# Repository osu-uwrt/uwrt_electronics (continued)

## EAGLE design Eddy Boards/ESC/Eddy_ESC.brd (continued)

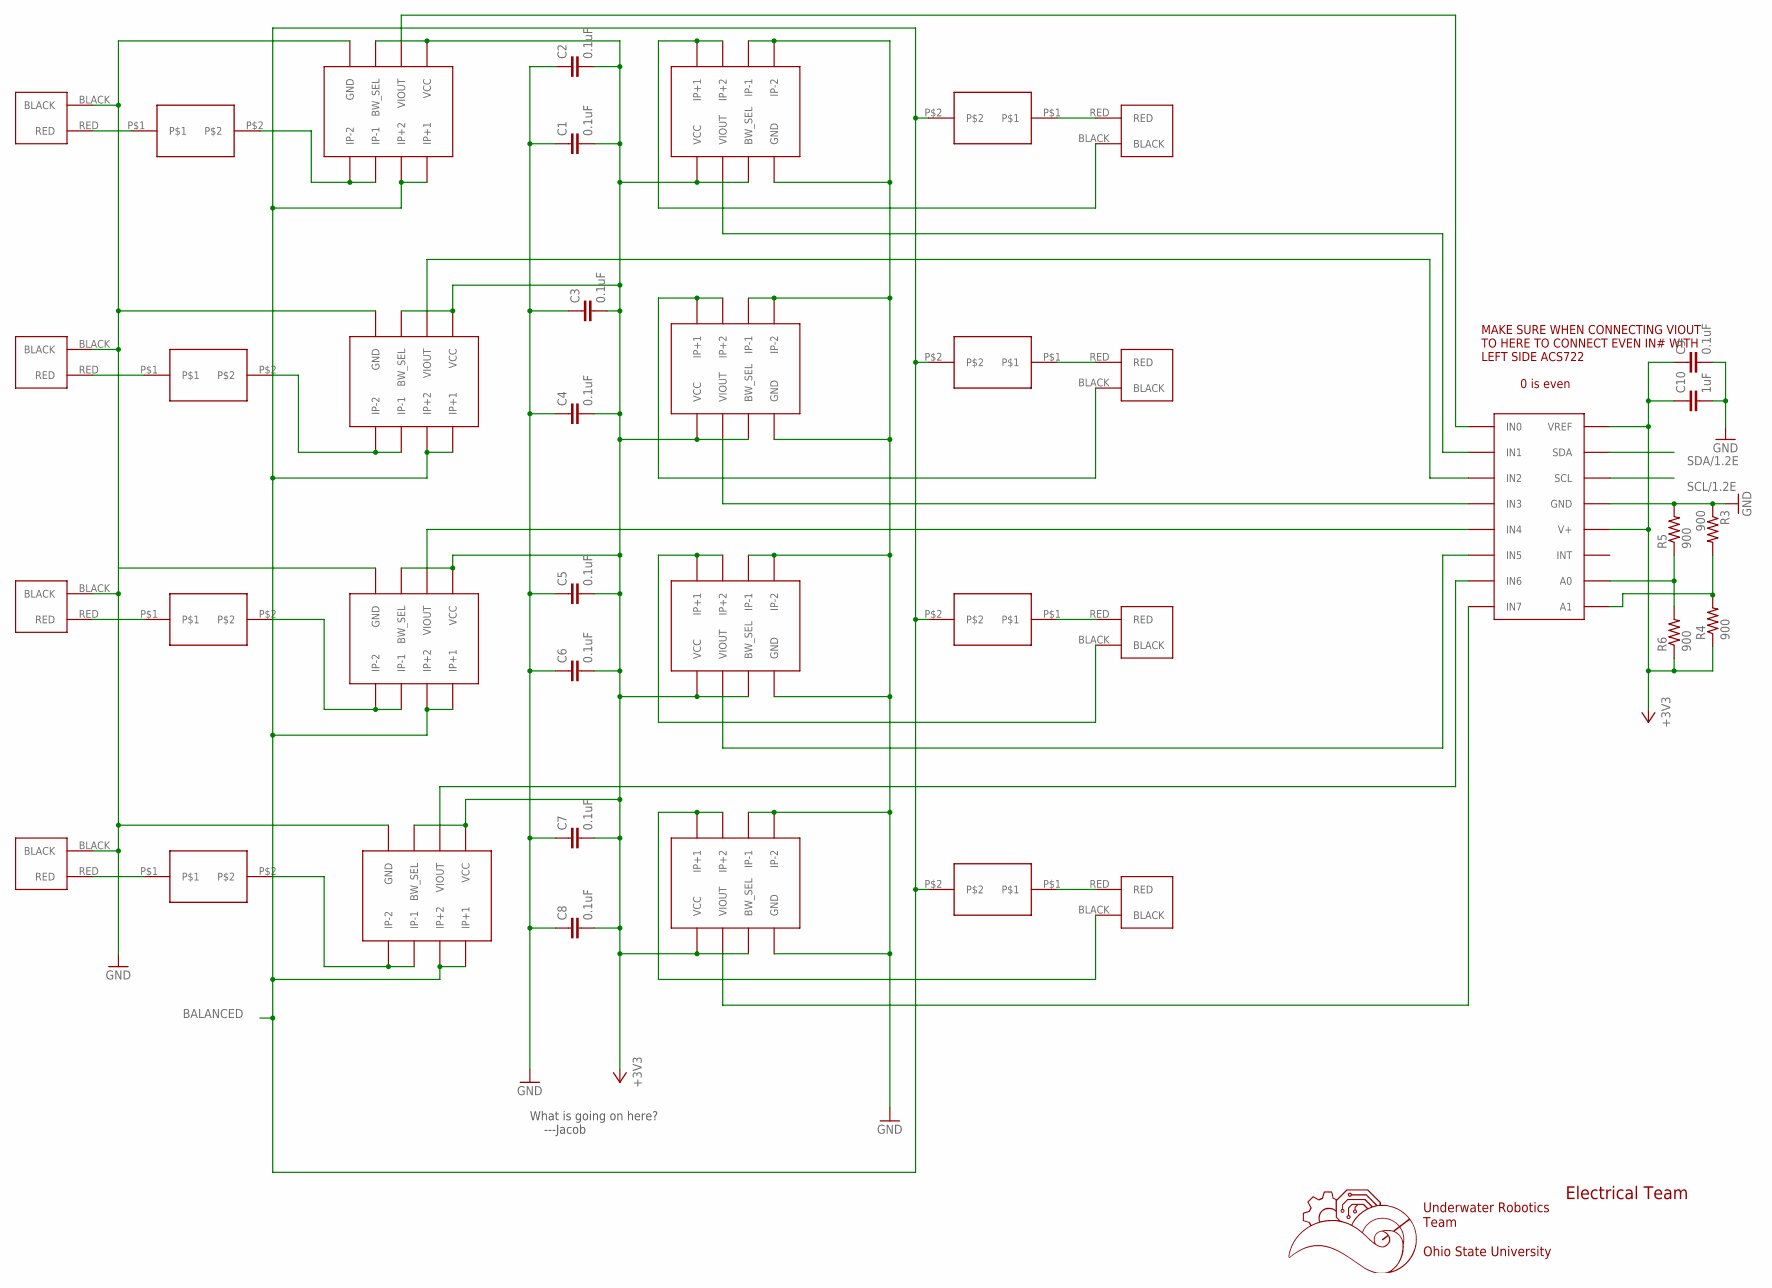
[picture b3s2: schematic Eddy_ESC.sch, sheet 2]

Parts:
C1, C2, C3, C4, C5, C6, C7, C8, C9: 0.1uF; C0603
C10: 1uF; C0603
R3, R4, R5, R6: 900; R0603
U$20, U$21, U$22, U$23, U$24, U$25, U$26, U$27: 1711725
U$28, U$29, U$30, U$31, U$32, U$33, U$34, U$35: ACS722; SOIC-8
U$36: ADC128D818; TSSOP-16
U$37, U$38, U$39, U$40, U$41, U$42, U$43, U$44: 1206SFH

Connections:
+3V3: C1.2, C2.2, C3.2, C4.2, C5.2, C6.2, C7.2, C8.2, C9.1, C10.1, R4.1, R6.1, U$28.BW_SEL, U$28.VCC, U$29.BW_SEL, U$29.VCC, U$30.BW_SEL, U$30.VCC, U$31.BW_SEL, U$31.VCC, U$32.BW_SEL, U$32.VCC, U$33.BW_SEL, U$33.VCC, U$34.BW_SEL, U$34.VCC, U$35.BW_SEL, U$35.VCC, U$36.V+, U$36.VREF; also elsewhere on the board
BALANCED: U$32.IP+1, U$32.IP+2, U$33.IP+1, U$33.IP+2, U$34.IP+1, U$34.IP+2, U$35.IP+1, U$35.IP+2, U$41.P$2, U$42.P$2, U$43.P$2, U$44.P$2
unnamed: U$20.BLACK, U$28.IP+1, U$28.IP+2
unnamed: U$21.BLACK, U$29.IP+1, U$29.IP+2
unnamed: U$34.VIOUT, U$36.IN4
unnamed: U$29.VIOUT, U$36.IN3
unnamed: U$22.BLACK, U$30.IP+1, U$30.IP+2
unnamed: U$33.IP-1, U$33.IP-2, U$38.P$2
unnamed: U$34.IP-1, U$34.IP-2, U$39.P$2
unnamed: U$31.VIOUT, U$36.IN7
unnamed: U$35.VIOUT, U$36.IN6
unnamed: U$30.VIOUT, U$36.IN5
unnamed: U$32.IP-1, U$32.IP-2, U$37.P$2
unnamed: U$35.IP-1, U$35.IP-2, U$40.P$2
unnamed: U$33.VIOUT, U$36.IN2
unnamed: U$28.VIOUT, U$36.IN1
unnamed: U$32.VIOUT, U$36.IN0
unnamed: U$24.RED, U$37.P$1
unnamed: U$25.RED, U$38.P$1
unnamed: U$26.RED, U$39.P$1
unnamed: U$27.RED, U$40.P$1
unnamed: U$20.RED, U$41.P$1
unnamed: U$21.RED, U$42.P$1
unnamed: U$22.RED, U$43.P$1
unnamed: U$23.RED, U$44.P$1
unnamed: R5.1, R6.2, U$36.A0
unnamed: R3.2, R4.2, U$36.A1
SCL/1.2E: U$36.SCL
SDA/1.2E: U$36.SDA

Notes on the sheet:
Underwater Robotics Team Ohio State University
Electrical Team
MAKE SURE WHEN CONNECTING VIOUT TO HERE TO CONNECT EVEN IN# WITH LEFT SIDE ACS722 0 is even
What is going on here? ---Jacob

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
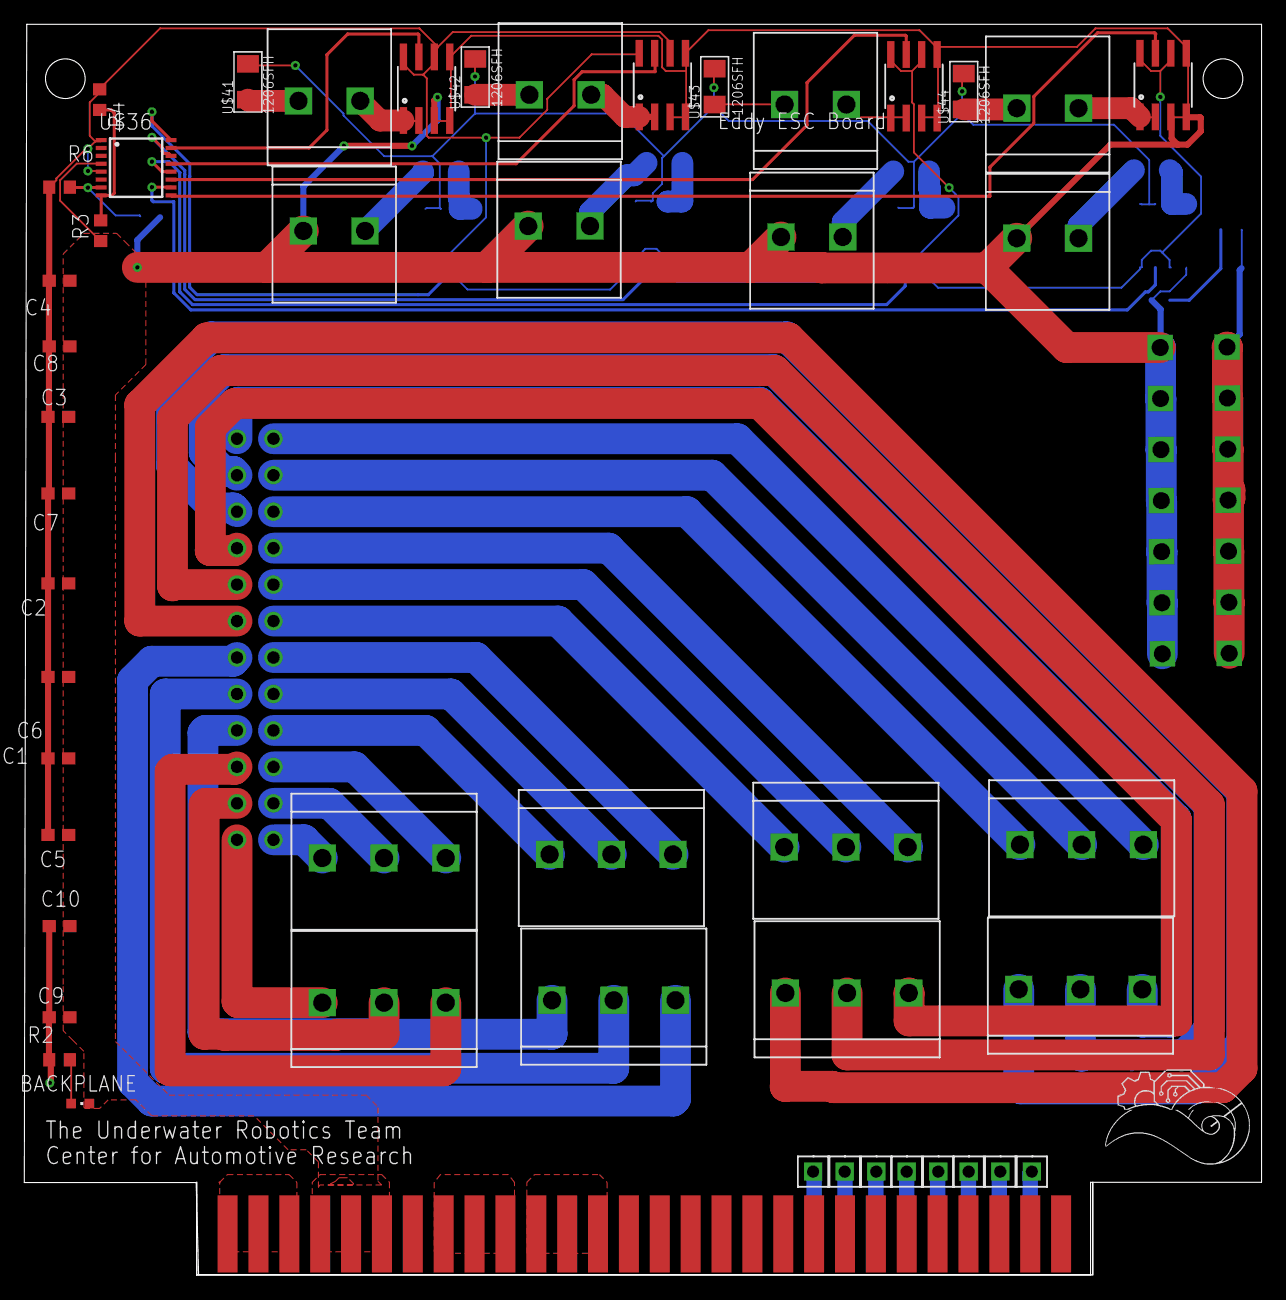
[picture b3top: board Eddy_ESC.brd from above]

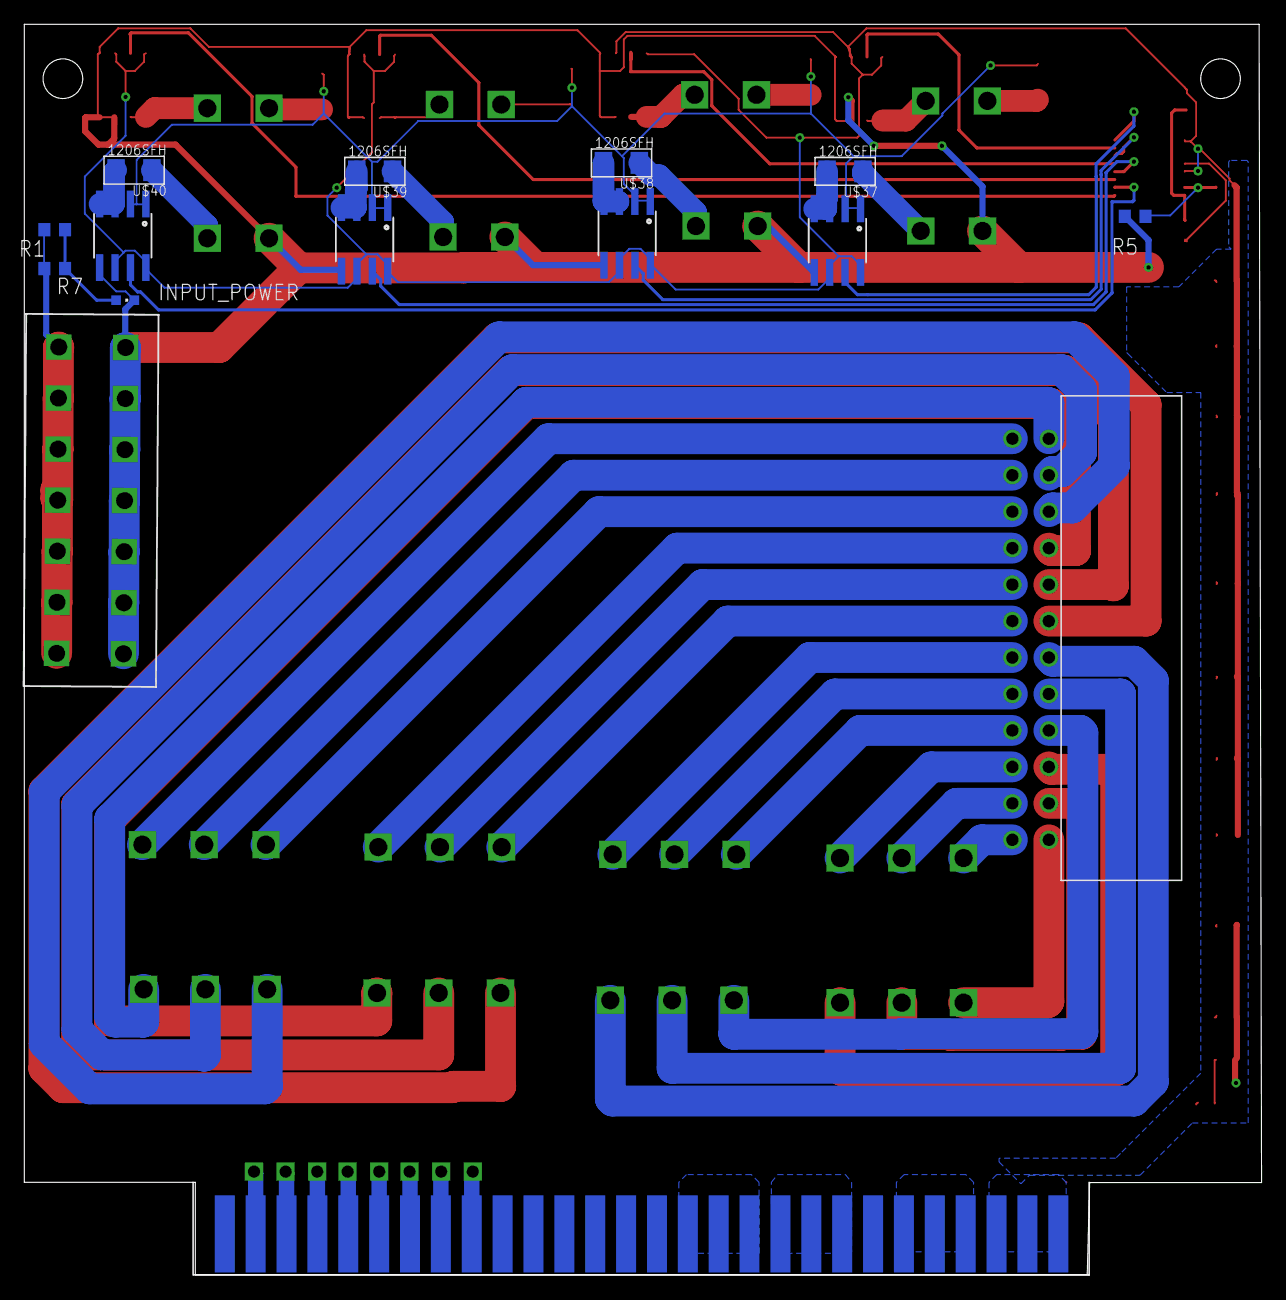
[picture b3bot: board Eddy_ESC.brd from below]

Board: 2 copper layers, 101.8 x 102.9 mm, 63 parts (14 on the bottom side), 64 nets.

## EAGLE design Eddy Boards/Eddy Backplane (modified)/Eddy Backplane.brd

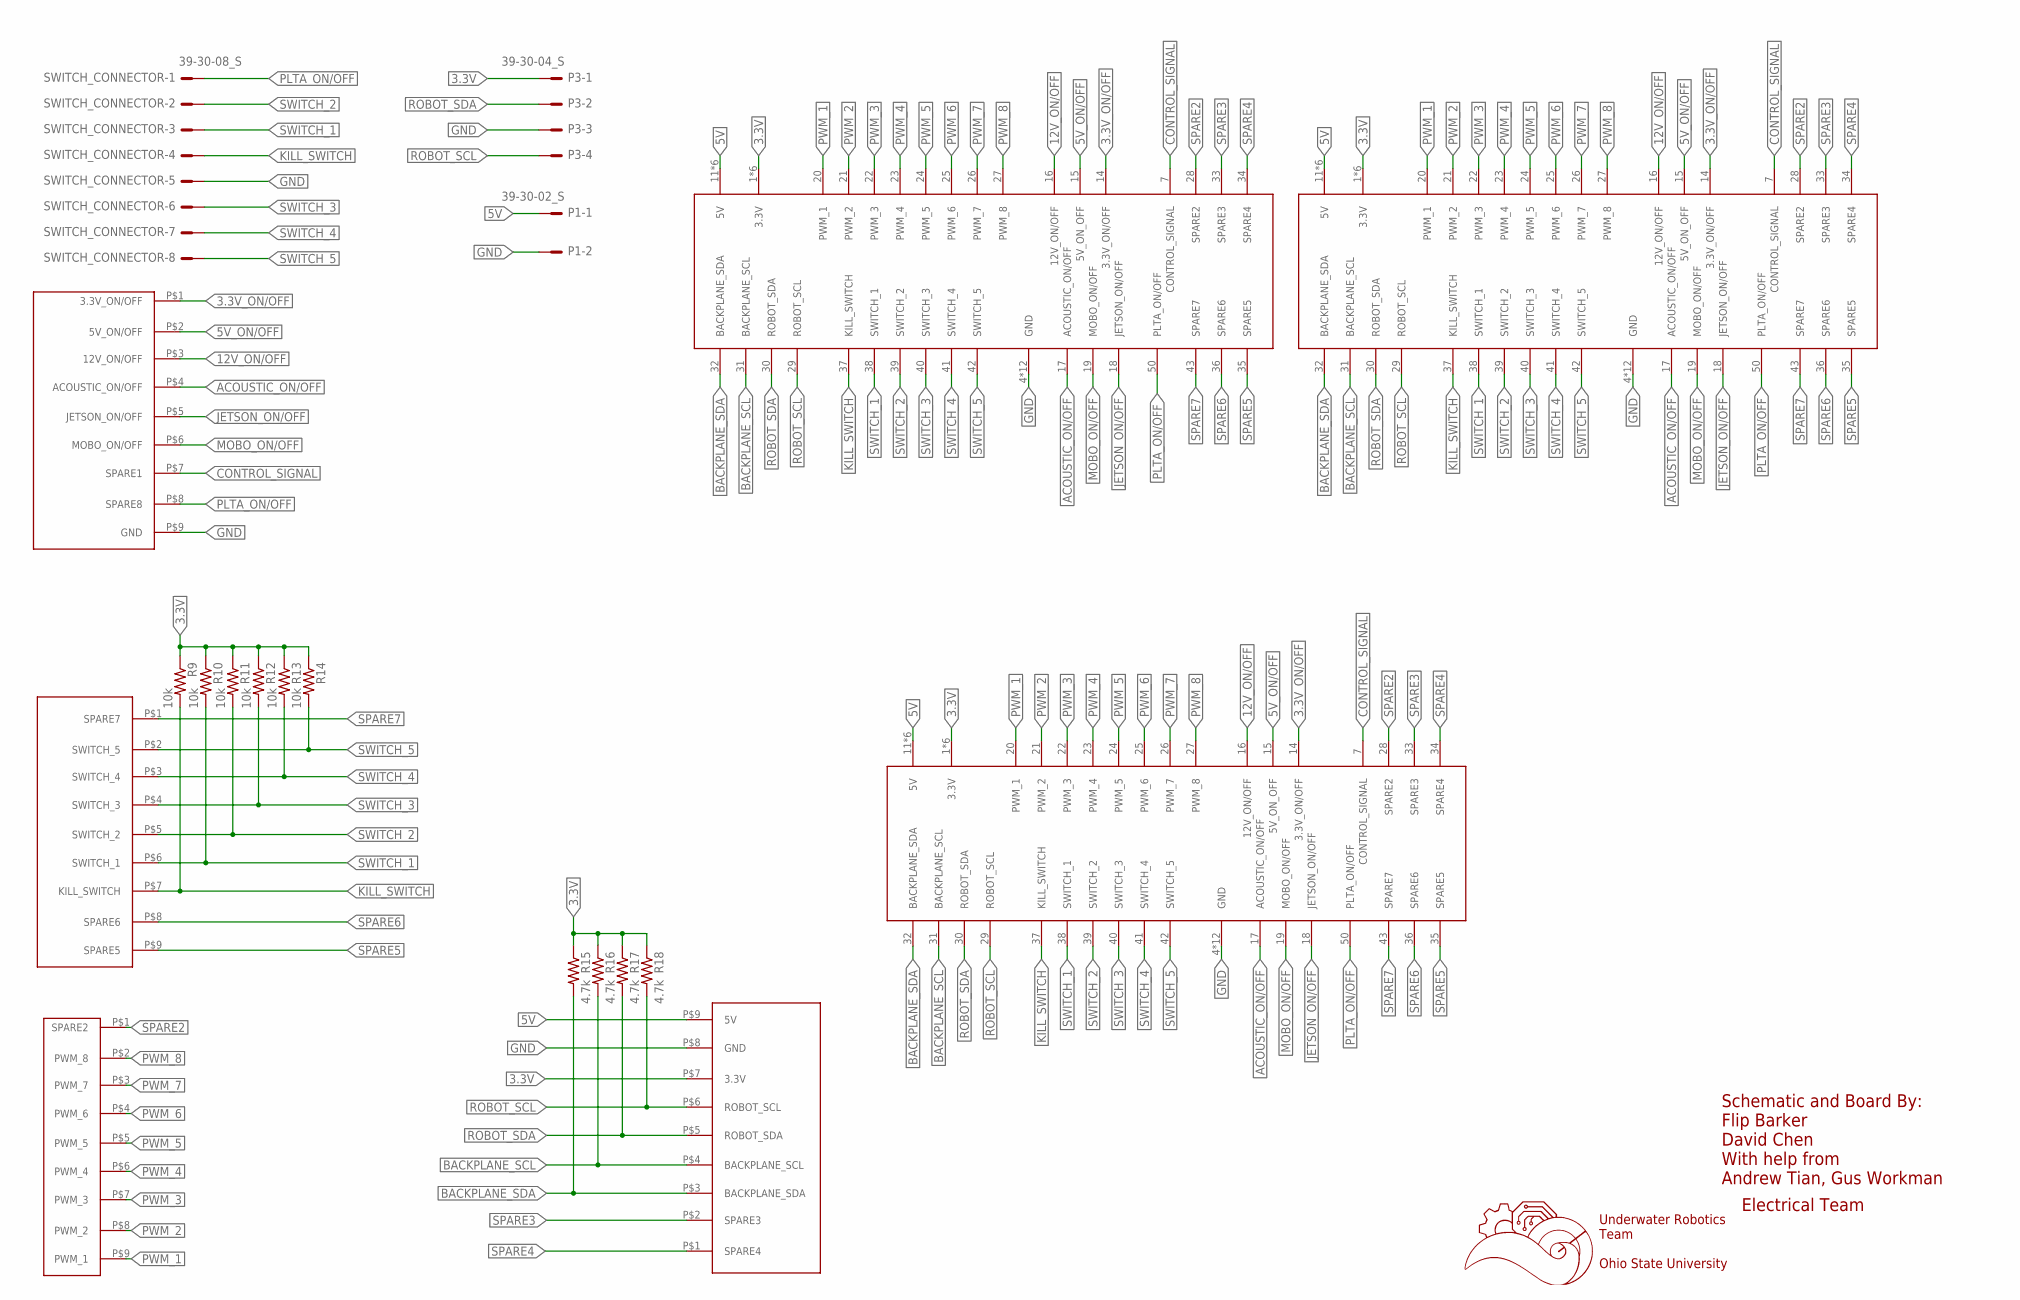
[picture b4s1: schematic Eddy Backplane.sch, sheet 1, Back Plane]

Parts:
P1: 39-30-02_S; 39-30-?02?
P3: 39-30-04_S; 39-30-?04?
PWR_ON: 929870-01-09_3; 929852-01-09_1ROW
R9, R10, R11, R12, R13, R14: 10k; R0603
R15, R16, R17, R18: 4.7k; R0603
SWITCH_CONN: 929870-01-09_1; 929852-01-09_1ROW
SWITCH_CONNECTOR: 39-30-08_S; 39-30-?08?
U$1, U$2, U$3: 5530843-FEMALE; 5530843-6-BACKPLANEMATE
U$6: 929870-01-09_2; 929852-01-09_1ROW
U$8: 929870-01-09_4; 929852-01-09_1ROW

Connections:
3.3V: P3.1, R9.1, R10.1, R11.1, R12.1, R13.1, R14.1, R15.1, R16.1, R17.1, R18.1, U$1.1 (3.3V), U$1.2 (3.3V), U$1.3 (3.3V), U$1.54 (3.3V), U$1.55 (3.3V), U$1.56 (3.3V), U$2.1 (3.3V), U$2.2 (3.3V), U$2.3 (3.3V), U$2.54 (3.3V), U$2.55 (3.3V), U$2.56 (3.3V), U$3.1 (3.3V), U$3.2 (3.3V), U$3.3 (3.3V), U$3.54 (3.3V), U$3.55 (3.3V), U$3.56 (3.3V), U$8.P$7 (3.3V); also elsewhere on the board
3.3V_ON/OFF: PWR_ON.P$1 (3.3V_ON/OFF), U$1.14 (3.3V_ON/OFF), U$2.14 (3.3V_ON/OFF), U$3.14 (3.3V_ON/OFF); also elsewhere on the board
5V: P1.1, U$1.11 (5V), U$1.12 (5V), U$1.13 (5V), U$1.44 (5V), U$1.45 (5V), U$1.46 (5V), U$2.11 (5V), U$2.12 (5V), U$2.13 (5V), U$2.44 (5V), U$2.45 (5V), U$2.46 (5V), U$3.11 (5V), U$3.12 (5V), U$3.13 (5V), U$3.44 (5V), U$3.45 (5V), U$3.46 (5V), U$8.P$9 (5V); also elsewhere on the board
5V_ON/OFF: PWR_ON.P$2 (5V_ON/OFF), U$1.15 (5V_ON_OFF), U$2.15 (5V_ON_OFF), U$3.15 (5V_ON_OFF); also elsewhere on the board
12V_ON/OFF: PWR_ON.P$3 (12V_ON/OFF), U$1.16 (12V_ON/OFF), U$2.16 (12V_ON/OFF), U$3.16 (12V_ON/OFF); also elsewhere on the board
ACOUSTIC_ON/OFF: PWR_ON.P$4 (ACOUSTIC_ON/OFF), U$1.17 (ACOUSTIC_ON/OFF), U$2.17 (ACOUSTIC_ON/OFF), U$3.17 (ACOUSTIC_ON/OFF)
BACKPLANE_SCL: R16.2, U$1.31 (BACKPLANE_SCL), U$2.31 (BACKPLANE_SCL), U$3.31 (BACKPLANE_SCL), U$8.P$4 (BACKPLANE_SCL); also elsewhere on the board
BACKPLANE_SDA: R15.2, U$1.32 (BACKPLANE_SDA), U$2.32 (BACKPLANE_SDA), U$3.32 (BACKPLANE_SDA), U$8.P$3 (BACKPLANE_SDA); also elsewhere on the board
CONTROL_SIGNAL: PWR_ON.P$7 (SPARE1), U$1.7 (CONTROL_SIGNAL), U$2.7 (CONTROL_SIGNAL), U$3.7 (CONTROL_SIGNAL); also elsewhere on the board
GND: P1.2, P3.3, PWR_ON.P$9 (GND), SWITCH_CONNECTOR.5, U$1.4 (GND), U$1.5 (GND), U$1.6 (GND), U$1.8 (GND), U$1.9 (GND), U$1.10 (GND), U$1.47 (GND), U$1.48 (GND), U$1.49 (GND), U$1.51 (GND), U$1.52 (GND), U$1.53 (GND), U$2.4 (GND), U$2.5 (GND), U$2.6 (GND), U$2.8 (GND), U$2.9 (GND), U$2.10 (GND), U$2.47 (GND), U$2.48 (GND), U$2.49 (GND), U$2.51 (GND), U$2.52 (GND), U$2.53 (GND), U$3.4 (GND), U$3.5 (GND), U$3.6 (GND), U$3.8 (GND), U$3.9 (GND), U$3.10 (GND), U$3.47 (GND), U$3.48 (GND), U$3.49 (GND), U$3.51 (GND), U$3.52 (GND), U$3.53 (GND), U$8.P$8 (GND); also elsewhere on the board
JETSON_ON/OFF: PWR_ON.P$5 (JETSON_ON/OFF), U$1.18 (JETSON_ON/OFF), U$2.18 (JETSON_ON/OFF), U$3.18 (JETSON_ON/OFF); also elsewhere on the board
KILL_SWITCH: R9.2, SWITCH_CONN.P$7 (KILL_SWITCH), SWITCH_CONNECTOR.4, U$1.37 (KILL_SWITCH), U$2.37 (KILL_SWITCH), U$3.37 (KILL_SWITCH); also elsewhere on the board
MOBO_ON/OFF: PWR_ON.P$6 (MOBO_ON/OFF), U$1.19 (MOBO_ON/OFF), U$2.19 (MOBO_ON/OFF), U$3.19 (MOBO_ON/OFF); also elsewhere on the board
PLTA_ON/OFF: PWR_ON.P$8 (SPARE8), SWITCH_CONNECTOR.1, U$1.50 (PLTA_ON/OFF), U$2.50 (PLTA_ON/OFF), U$3.50 (PLTA_ON/OFF)
PWM_1: U$1.20 (PWM_1), U$2.20 (PWM_1), U$3.20 (PWM_1), U$6.P$9 (PWM_1); also elsewhere on the board
PWM_2: U$1.21 (PWM_2), U$2.21 (PWM_2), U$3.21 (PWM_2), U$6.P$8 (PWM_2); also elsewhere on the board
PWM_3: U$1.22 (PWM_3), U$2.22 (PWM_3), U$3.22 (PWM_3), U$6.P$7 (PWM_3); also elsewhere on the board
PWM_4: U$1.23 (PWM_4), U$2.23 (PWM_4), U$3.23 (PWM_4), U$6.P$6 (PWM_4); also elsewhere on the board
PWM_5: U$1.24 (PWM_5), U$2.24 (PWM_5), U$3.24 (PWM_5), U$6.P$5 (PWM_5); also elsewhere on the board
PWM_6: U$1.25 (PWM_6), U$2.25 (PWM_6), U$3.25 (PWM_6), U$6.P$4 (PWM_6); also elsewhere on the board
PWM_7: U$1.26 (PWM_7), U$2.26 (PWM_7), U$3.26 (PWM_7), U$6.P$3 (PWM_7); also elsewhere on the board
PWM_8: U$1.27 (PWM_8), U$2.27 (PWM_8), U$3.27 (PWM_8), U$6.P$2 (PWM_8); also elsewhere on the board
ROBOT_SCL: P3.4, R18.2, U$1.29 (ROBOT_SCL), U$2.29 (ROBOT_SCL), U$3.29 (ROBOT_SCL), U$8.P$6 (ROBOT_SCL); also elsewhere on the board
ROBOT_SDA: P3.2, R17.2, U$1.30 (ROBOT_SDA), U$2.30 (ROBOT_SDA), U$3.30 (ROBOT_SDA), U$8.P$5 (ROBOT_SDA); also elsewhere on the board
SPARE2: U$1.28 (SPARE2), U$2.28 (SPARE2), U$3.28 (SPARE2), U$6.P$1 (SPARE2)
SPARE3: U$1.33 (SPARE3), U$2.33 (SPARE3), U$3.33 (SPARE3), U$8.P$2 (SPARE3)
SPARE4: U$1.34 (SPARE4), U$2.34 (SPARE4), U$3.34 (SPARE4), U$8.P$1 (SPARE4)
SPARE5: SWITCH_CONN.P$9 (SPARE5), U$1.35 (SPARE5), U$2.35 (SPARE5), U$3.35 (SPARE5)
SPARE6: SWITCH_CONN.P$8 (SPARE6), U$1.36 (SPARE6), U$2.36 (SPARE6), U$3.36 (SPARE6)
SPARE7: SWITCH_CONN.P$1 (SPARE7), U$1.43 (SPARE7), U$2.43 (SPARE7), U$3.43 (SPARE7)
SWITCH_1: R10.2, SWITCH_CONN.P$6 (SWITCH_1), SWITCH_CONNECTOR.3, U$1.38 (SWITCH_1), U$2.38 (SWITCH_1), U$3.38 (SWITCH_1); also elsewhere on the board
SWITCH_2: R11.2, SWITCH_CONN.P$5 (SWITCH_2), SWITCH_CONNECTOR.2, U$1.39 (SWITCH_2), U$2.39 (SWITCH_2), U$3.39 (SWITCH_2); also elsewhere on the board
SWITCH_3: R12.2, SWITCH_CONN.P$4 (SWITCH_3), SWITCH_CONNECTOR.6, U$1.40 (SWITCH_3), U$2.40 (SWITCH_3), U$3.40 (SWITCH_3); also elsewhere on the board
SWITCH_4: R13.2, SWITCH_CONN.P$3 (SWITCH_4), SWITCH_CONNECTOR.7, U$1.41 (SWITCH_4), U$2.41 (SWITCH_4), U$3.41 (SWITCH_4); also elsewhere on the board
SWITCH_5: R14.2, SWITCH_CONN.P$2 (SWITCH_5), SWITCH_CONNECTOR.8, U$1.42 (SWITCH_5), U$2.42 (SWITCH_5), U$3.42 (SWITCH_5); also elsewhere on the board

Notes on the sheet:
Underwater Robotics Team Ohio State University
Electrical Team
Schematic and Board By: Flip Barker David Chen With help from Andrew Tian, Gus Workman

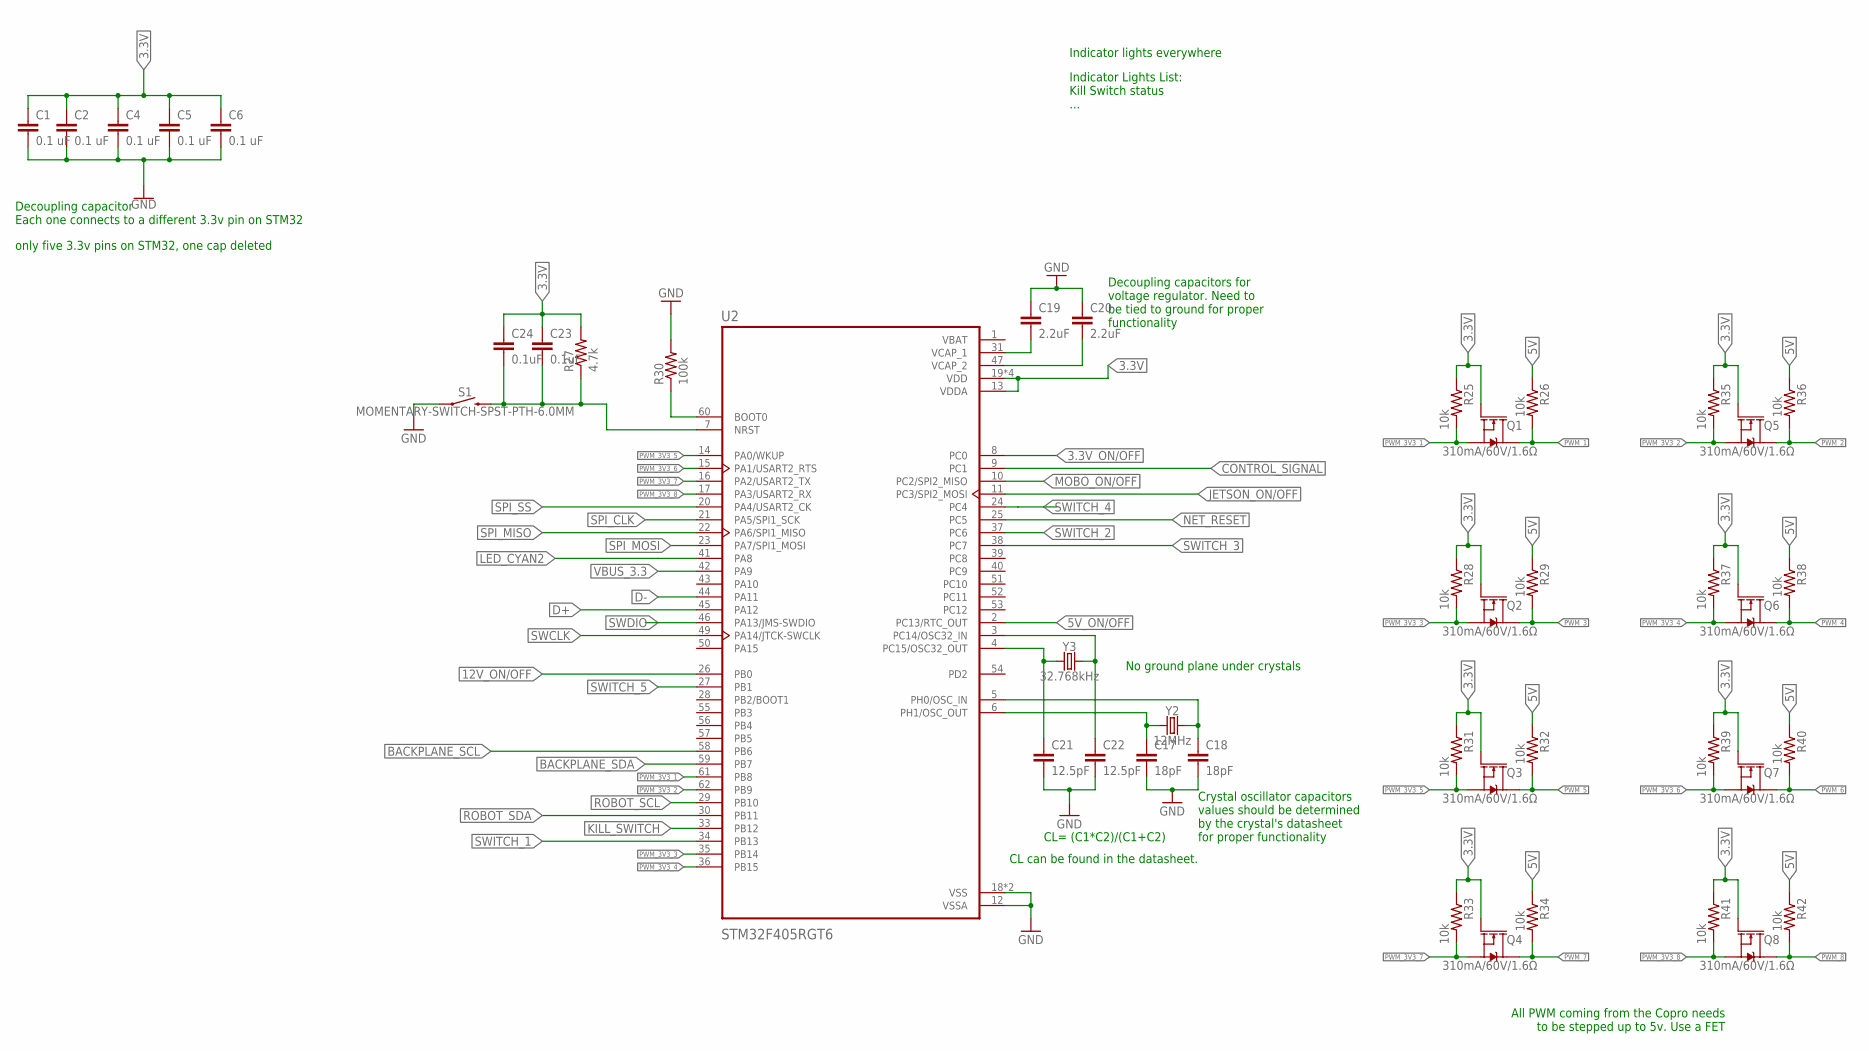
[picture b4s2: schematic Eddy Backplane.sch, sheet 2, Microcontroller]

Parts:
C1, C2, C4, C5, C6: 0.1 uF; C0603
C17, C18: 18pF; C0603
C19, C20: 2.2uF; C0603
C21, C22: 12.5pF; C0603
C23, C24: 0.1uF; C0603
Q1, Q2, Q3, Q4, Q5, Q6, Q7, Q8: 310mA/60V/1.6Ω; SOT323
R25, R26, R28, R29, R31, R32, R33, R34, R35, R36, R37, R38, R39, R40, R41, R42: 10k; R0603
R27: 4.7k; R0603
R30: 100k; R0603
S1: MOMENTARY-SWITCH-SPST-PTH-6.0MM; TACTILE_SWITCH_PTH_6.0MM
U2: STM32F405RGT6; QFP50P1200X1200X160-64N
Y2: 12MHz; HC49US
Y3: 32.768kHz; CRYSTAL-SMD-3.2X1.5MM

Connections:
3.3V: C1.1, C2.1, C4.1, C5.1, C6.1, C23.1, C24.1, Q1.1 (G), Q2.1 (G), Q3.1 (G), Q4.1 (G), Q5.1 (G), Q6.1 (G), Q7.1 (G), Q8.1 (G), R25.1, R27.2, R28.1, R31.1, R33.1, R35.1, R37.1, R39.1, R41.1, U2.13 (VDDA), U2.19 (VDD), U2.32 (VDD), U2.48 (VDD), U2.64 (VDD); also elsewhere on the board
3.3V_ON/OFF: U2.8 (PC0); also elsewhere on the board
5V: R26.1, R29.1, R32.1, R34.1, R36.1, R38.1, R40.1, R42.1; also elsewhere on the board
5V_ON/OFF: U2.2 (PC13/RTC_OUT); also elsewhere on the board
12V_ON/OFF: U2.26 (PB0); also elsewhere on the board
BACKPLANE_SCL: U2.58 (PB6); also elsewhere on the board
BACKPLANE_SDA: U2.59 (PB7); also elsewhere on the board
CONTROL_SIGNAL: U2.9 (PC1); also elsewhere on the board
D+: U2.45 (PA12); also elsewhere on the board
D-: U2.44 (PA11); also elsewhere on the board
GND: C1.2, C2.2, C4.2, C5.2, C6.2, C17.2, C18.2, C19.1, C20.1, C21.2, C22.2, R30.2, S1.1, U2.12 (VSSA), U2.18 (VSS), U2.63 (VSS); also elsewhere on the board
JETSON_ON/OFF: U2.11 (PC3/SPI2_MOSI); also elsewhere on the board
KILL_SWITCH: U2.33 (PB12); also elsewhere on the board
LED_CYAN2: U2.41 (PA8)
MOBO_ON/OFF: U2.10 (PC2/SPI2_MISO); also elsewhere on the board
unnamed: C17.1, U2.6 (PH1/OSC_OUT), Y2.1
unnamed: C18.1, U2.5 (PH0/OSC_IN), Y2.2
unnamed: C20.2, U2.47 (VCAP_2)
unnamed: C19.2, U2.31 (VCAP_1)
unnamed: C21.1, U2.4 (PC15/OSC32_OUT), Y3.P$1 (1)
unnamed: C22.1, U2.3 (PC14/OSC32_IN), Y3.P$2 (2)
unnamed: R30.1, U2.60 (BOOT0)
unnamed: C23.2, C24.2, R27.1, S1.3 (2), U2.7 (NRST)
NET_RESET: U2.25 (PC5); also elsewhere on the board
PWM_1: Q1.3 (D), R26.2; also elsewhere on the board
PWM_2: Q5.3 (D), R36.2; also elsewhere on the board
PWM_3: Q2.3 (D), R29.2; also elsewhere on the board
PWM_3V3_1: Q1.2 (S), R25.2, U2.61 (PB8)
PWM_3V3_2: Q5.2 (S), R35.2, U2.62 (PB9)
PWM_3V3_3: Q2.2 (S), R28.2, U2.35 (PB14)
PWM_3V3_4: Q6.2 (S), R37.2, U2.36 (PB15)
PWM_3V3_5: Q3.2 (S), R31.2, U2.14 (PA0/WKUP)
PWM_3V3_6: Q7.2 (S), R39.2, U2.15 (PA1/USART2_RTS)
PWM_3V3_7: Q4.2 (S), R33.2, U2.16 (PA2/USART2_TX)
PWM_3V3_8: Q8.2 (S), R41.2, U2.17 (PA3/USART2_RX)
PWM_4: Q6.3 (D), R38.2; also elsewhere on the board
PWM_5: Q3.3 (D), R32.2; also elsewhere on the board
PWM_6: Q7.3 (D), R40.2; also elsewhere on the board
PWM_7: Q4.3 (D), R34.2; also elsewhere on the board
PWM_8: Q8.3 (D), R42.2; also elsewhere on the board
ROBOT_SCL: U2.29 (PB10); also elsewhere on the board
ROBOT_SDA: U2.30 (PB11); also elsewhere on the board
SPI_CLK: U2.21 (PA5/SPI1_SCK); also elsewhere on the board
SPI_MISO: U2.22 (PA6/SPI1_MISO); also elsewhere on the board
SPI_MOSI: U2.23 (PA7/SPI1_MOSI); also elsewhere on the board
SPI_SS: U2.20 (PA4/USART2_CK); also elsewhere on the board
SWCLK: U2.49 (PA14/JTCK-SWCLK); also elsewhere on the board
SWDIO: U2.46 (PA13/JMS-SWDIO); also elsewhere on the board
SWITCH_1: U2.34 (PB13); also elsewhere on the board
SWITCH_2: U2.37 (PC6); also elsewhere on the board
SWITCH_3: U2.38 (PC7); also elsewhere on the board
SWITCH_4: U2.24 (PC4); also elsewhere on the board
SWITCH_5: U2.27 (PB1); also elsewhere on the board
VBAT: U2.1 (VBAT)
VBUS_3.3: U2.42 (PA9); also elsewhere on the board

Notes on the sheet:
Decoupling capacitor Each one connects to a different 3.3v pin on STM32
Indicator lights everywhere
Decoupling capacitors for voltage regulator. Need to be tied to ground for proper functionality
Crystal oscillator capacitors values should be determined by the crystal's datasheet for proper functionality
All PWM coming from the Copro needs to be stepped up to 5v. Use a FET
CL= (C1*C2)/(C1+C2)
CL can be found in the datasheet.
No ground plane under crystals
Indicator Lights List: Kill Switch status ...
only five 3.3v pins on STM32, one cap deleted

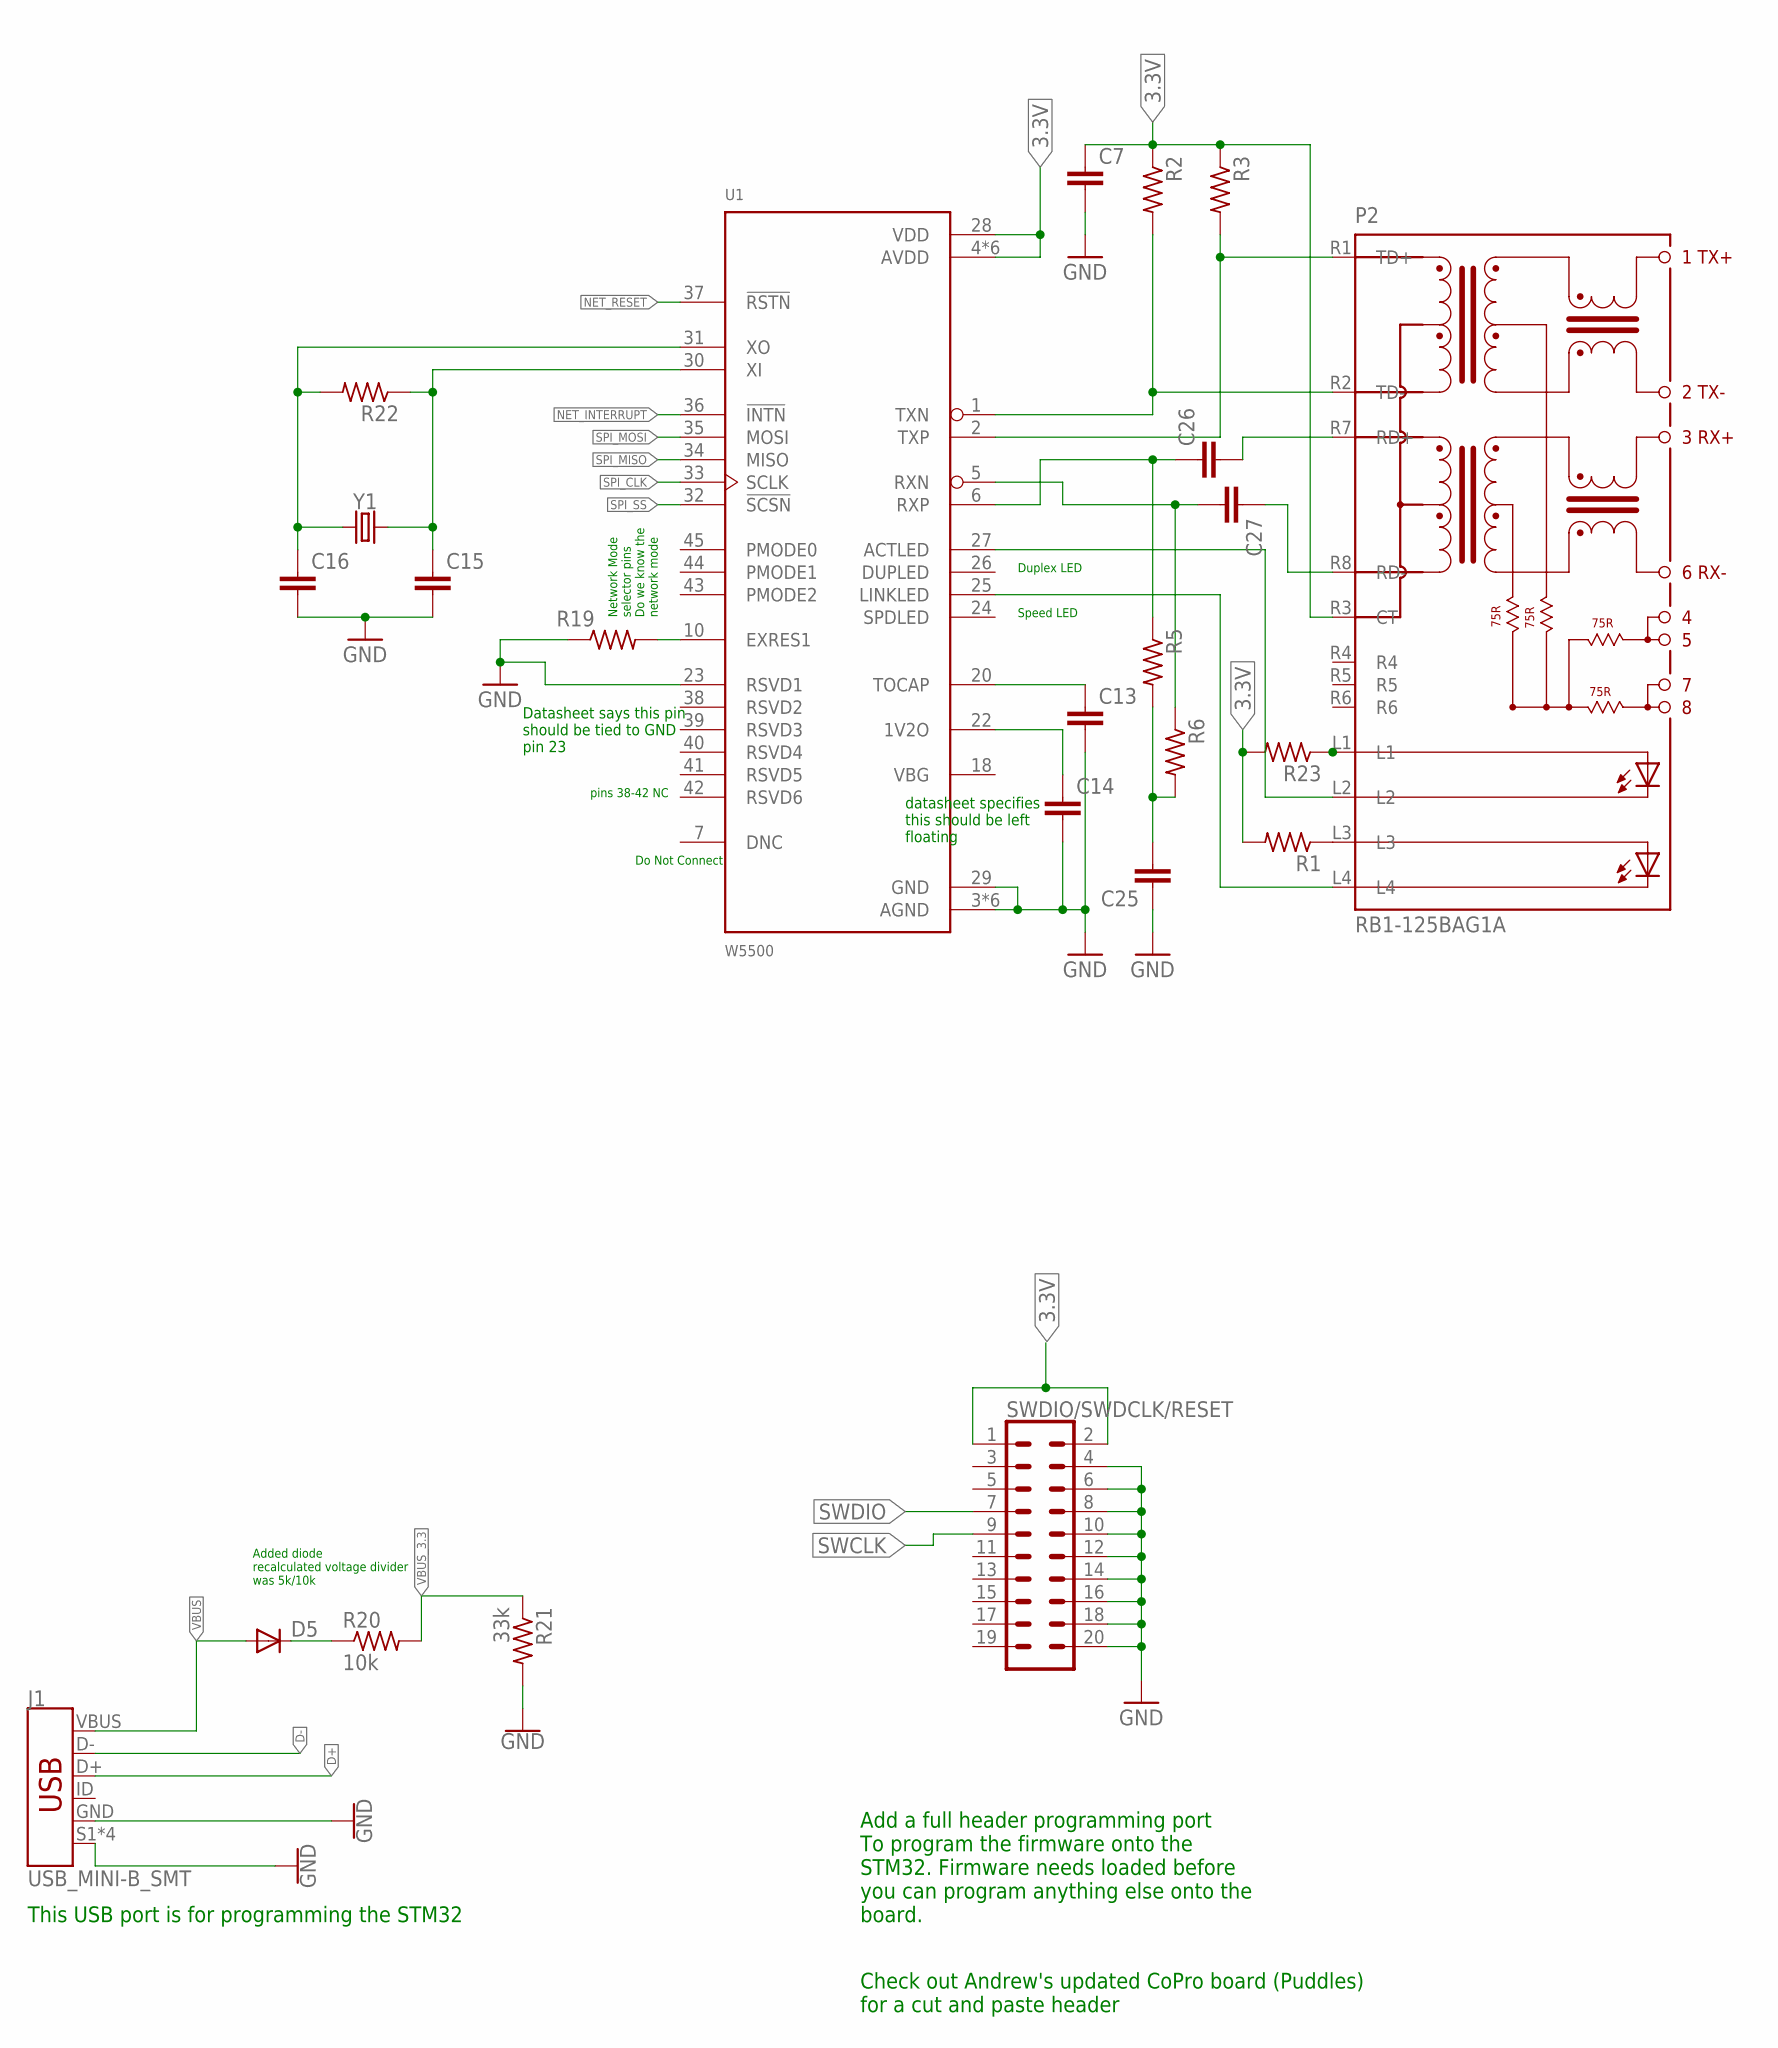
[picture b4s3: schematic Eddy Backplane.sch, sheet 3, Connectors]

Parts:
C7, C13, C14, C15, C16, C25, C26, C27: C-EUC0603; C0603
D5: DIODE-SMB; SMB
J1: USB_MINI-B_SMT; USB-MINIB
P2: RB1-125BAG1A; WIZNET_RB1-125BAG1A
R1, R2, R3, R5, R6, R19, R22, R23: R-US_R0603; R0603
R20: 10k; R0603
R21: 33k; R0603
SWDIO/SWDCLK/RESET: CONN_10X2; 2X10
U1: W5500; QFP50P900X900X160-48N
Y1: CRYSTALPTH-HC49US; HC49US

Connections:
3.3V: C7.1, P2.R3 (CT), R1.2, R2.1, R3.1, R23.2, SWDIO/SWDCLK/RESET.1, SWDIO/SWDCLK/RESET.2, U1.4 (AVDD), U1.8 (AVDD), U1.11 (AVDD), U1.15 (AVDD), U1.17 (AVDD), U1.21 (AVDD), U1.28 (VDD); also elsewhere on the board
D+: J1.D+; also elsewhere on the board
D-: J1.D-; also elsewhere on the board
GND: C7.2, C13.2, C14.2, C15.2, C16.2, C25.1, J1.GND, J1.S1 (SHIELD), J1.S2 (SHIELD), J1.S3 (SHIELD), J1.S4 (SHIELD), R19.1, R21.2, SWDIO/SWDCLK/RESET.4, SWDIO/SWDCLK/RESET.6, SWDIO/SWDCLK/RESET.8, SWDIO/SWDCLK/RESET.10, SWDIO/SWDCLK/RESET.12, SWDIO/SWDCLK/RESET.14, SWDIO/SWDCLK/RESET.16, SWDIO/SWDCLK/RESET.18, SWDIO/SWDCLK/RESET.20, U1.3 (AGND), U1.9 (AGND), U1.14 (AGND), U1.16 (AGND), U1.19 (AGND), U1.23 (RSVD1), U1.29 (GND), U1.48 (AGND); also elsewhere on the board
unnamed: C14.1, U1.22 (1V2O)
unnamed: D5.C, R20.1
unnamed: C15.1, R22.1, U1.30 (XI), Y1.2
unnamed: C16.1, R22.2, U1.31 (XO), Y1.1
unnamed: P2.L4, U1.25 (LINKLED)
unnamed: P2.L2, U1.27 (ACTLED)
unnamed: C13.1, U1.20 (TOCAP)
unnamed: R19.2, U1.10 (EXRES1)
unnamed: P2.L1, R23.1
unnamed: P2.L3, R1.1
unnamed: C25.2, R5.2, R6.2
unnamed: P2.R1 (TD+), R3.2, U1.2 (TXP)
unnamed: P2.R2 (TD-), R2.2, U1.1 (TXN)
unnamed: C26.2, P2.R7 (RD+)
unnamed: C26.1, R5.1, U1.6 (RXP)
unnamed: C27.2, R6.1, U1.5 (RXN)
unnamed: C27.1, P2.R8 (RD-)
NET_INTERRUPT: U1.36 (!INTN)
NET_RESET: U1.37 (!RSTN); also elsewhere on the board
SPI_CLK: U1.33 (SCLK); also elsewhere on the board
SPI_MISO: U1.34 (MISO); also elsewhere on the board
SPI_MOSI: U1.35 (MOSI); also elsewhere on the board
SPI_SS: U1.32 (!SCSN); also elsewhere on the board
SWCLK: SWDIO/SWDCLK/RESET.9; also elsewhere on the board
SWDIO: SWDIO/SWDCLK/RESET.7; also elsewhere on the board
VBUS: D5.A, J1.VBUS
VBUS_3.3: R20.2, R21.1; also elsewhere on the board

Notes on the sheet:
This USB port is for programming the STM32
Add a full header programming port To program the firmware onto the STM32. Firmware needs loaded before you can program anything else onto the board.
Check out Andrew's updated CoPro board (Puddles) for a cut and paste header
datasheet specifies this should be left floating
Datasheet says this pin should be tied to GND pin 23
pins 38-42 NC
Do Not Connect
Duplex LED
Speed LED
Network Mode selector pins Do we know the network mode
Added diode recalculated voltage divider was 5k/10k
